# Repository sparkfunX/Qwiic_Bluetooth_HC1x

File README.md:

SparkFun Qwiic Bluetooth
========================================

[*SparkX Qwiic Bluetooth (SPX-14840)*](https://www.sparkfun.com/products/14840)

Bluetooth is a great addition to a variety of projects, but the interface to most Bluetooth modules is through a serial UART, which can be a real bummer -- serial port availability can be limited and they're not always super-reliable. The Qwiic Bluetooth aims resolve that issue by providing an I<sup>2</sup>C interface to the HM-13 Bluetooth module.

This board's HM-13 Bluetooth module supports both SPP (Serial Port Profile) and BLE (Bluetooth low-energy) Bluetooth profiles via Bluetooth 4.0. The HM-13's support for BLE means it's compatible with any smartphone.  Or you can connect it to a computer via the old standard -- SPP -- and use it as a transparent Bluetooth data gateway. You can even use it in dual-mode, connected to a pair of devices simultaneously!

The board also features an ATTiny85, which has custom firmware to translate between between I<sup>2</sup>C and serial. There are a pair of Qwiic connectors, which allow you to string a variety of sensors up to a single I<sup>2</sup>C bus. Finally, a green "CON" LED indicates connection status -- blinking when disconnected and solid when connected.

Check out our [HM-13 Arduino library](https://github.com/sparkfun/SparkFun_HM1X_Bluetooth_Arduino_Library) for help developing Bluetooth app of your own! There are a handful of "Qwiic" examples, which demonstrate how to set up a simple serial passthrough, adjust some of the module settings, and even set it up as an **iBeacon**.

SparkFun labored with love to create this code. Feel like supporting open source hardware? 
Buy a [breakout board](https://www.sparkfun.com/products/14840) from SparkFun!

Repository Contents
-------------------

* **/Documents** - Datasheets
* **/Firmware** - I<sup>2</sup>C-to-Serial firmware for ATTiny85 (Arduino code)
* **/Hardware** - Eagle design files (.brd, .sch)

License Information
-------------------

This product is _**open source**_! 

If you have any questions or concerns on licensing, please contact techsupport@sparkfun.com.

Please use, reuse, and modify these files as you see fit. Please maintain attribution to SparkFun Electronics and release any derivative under the same license.

Distributed as-is; no warranty is given.

- Your friends at SparkFun.

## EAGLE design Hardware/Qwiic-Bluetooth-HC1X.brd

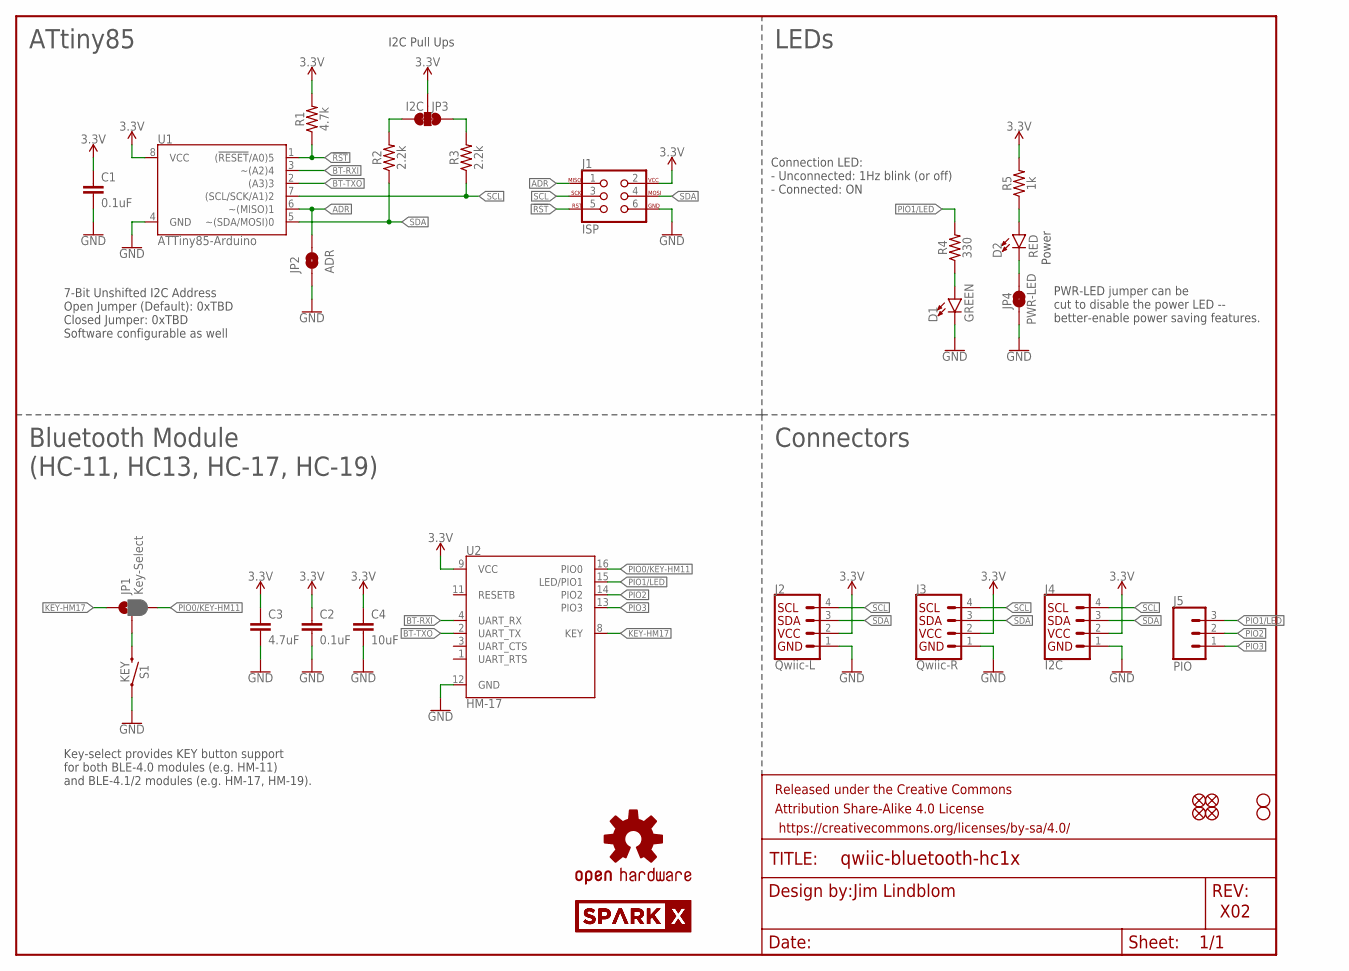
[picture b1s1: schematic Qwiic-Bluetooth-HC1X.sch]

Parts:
C1, C2: 0.1uF; 0603
C3: 4.7uF; 0603
C4: 10uF; 0603
D1: GREEN; LED-0603
D2: RED; LED-0603
FRAME1: FRAME-LETTER; CREATIVE_COMMONS
J1: ISP; 2X3_TEST_POINTS
J2: Qwiic-L; 1X04_1MM_RA
J3: Qwiic-R; 1X04_1MM_RA
J4: I2C; 1X04_NO_SILK
J5: PIO; 1X03_NO_SILK
JP1: Key-Select; SMT-JUMPER_3_1-NC_PASTE_NO-SILK
JP2: ADR; SMT-JUMPER_2_NO_NO-SILK
JP3: I2C; SMT-JUMPER_3_2-NC_TRACE_NO-SILK
JP4: PWR-LED; SMT-JUMPER_2_NC_TRACE_NO-SILK
JP5, JP6, JP7, JP8: FIDUCIALUFIDUCIAL; FIDUCIAL-MICRO
JP11, JP12: STAND-OFF
LOGO1: OSHW-LOGOMINI; OSHW-LOGO-MINI
LOGO2, LOGO3: SPARKX-LOGO4; SPARKX-MEDIUM
R1: 4.7k; 0603
R2, R3: 2.2k; 0603
R4: 330; 0603
R5: 1k; 0603
S1: KEY; TACTILE_SWITCH_SMD_4.6X2.8MM
U1: ATTiny85-Arduino; SO08-EIAJ_MCU
U2: HM-17; HM-11

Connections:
3.3V: C1.1, C2.1, C3.1, C4.1, J1.2, J2.2, J3.2, J4.2 (VCC), JP3.2, R1.2, R5.2, U1.8 (VCC), U2.9 (VCC)
!RST: J1.5, R1.1, U1.1 ((!RESET!/A0)5)
ADR: J1.1, JP2.2, U1.6 (~(MISO)1)
BT-RXI: U1.3 (~(A2)4), U2.4 (UART_RX)
BT-TXO: U1.2 ((A3)3), U2.2 (UART_TX)
GND: C1.2, C2.2, C3.2, C4.2, D1.C, J1.6, J2.1, J3.1, J4.1 (GND), JP2.1, JP4.1, S1.1, S1.2 (1), U1.4 (GND), U2.12 (GND)
KEY-HM17: JP1.1, U2.8 (KEY)
unnamed: D2.C, JP4.2
unnamed: D1.A, R4.1
unnamed: D2.A, R5.1
unnamed: JP1.2, S1.3 (2), S1.4 (2)
PIO0/KEY-HM11: JP1.3, U2.16 (PIO0)
PIO1/LED: J5.3, R4.2, U2.15 (LED/PIO1)
PIO2: J5.2, U2.14 (PIO2)
PIO3: J5.1, U2.13 (PIO3)
SCL: J1.3, J2.4, J3.4, J4.4 (SCL), R3.1, U1.7 ((SCL/SCK/A1)2)
SCL_PU1: JP3.1, R3.2
SDA: J1.4, J2.3, J3.3, J4.3 (SDA), R2.1, U1.5 (~(SDA/MOSI)0)
SDA_PU1: JP3.3, R2.2

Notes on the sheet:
7-Bit Unshifted I2C Address Open Jumper (Default): 0xTBD Closed Jumper: 0xTBD Software configurable as well
I2C Pull Ups
ATtiny85
Jim Lindblom
X02
Power
Key-select provides KEY button support for both BLE-4.0 modules (e.g. HM-11) and BLE-4.1/2 modules (e.g. HM-17, HM-19).
PWR-LED jumper can be cut to disable the power LED -- better-enable power saving features.
Bluetooth Module (HC-11, HC13, HC-17, HC-19)
LEDs
Connectors
Connection LED: - Unconnected: 1Hz blink (or off) - Connected: ON

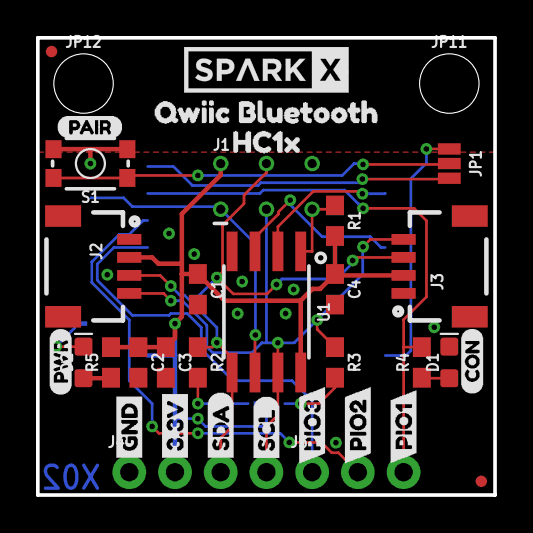
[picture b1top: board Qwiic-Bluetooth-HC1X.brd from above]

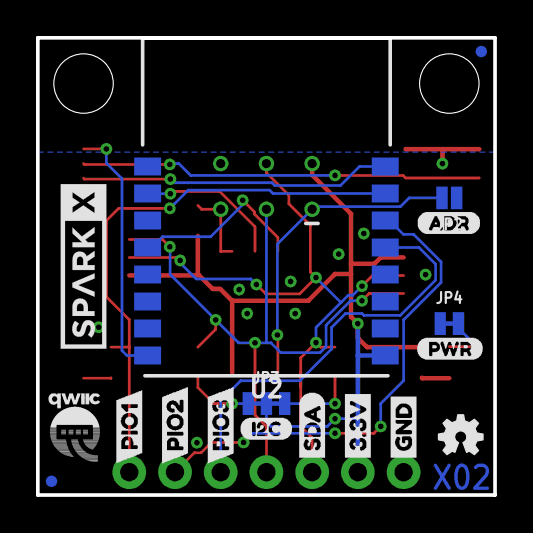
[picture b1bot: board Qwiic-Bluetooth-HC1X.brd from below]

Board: 2 copper layers, 25.4 x 25.4 mm, 55 parts (18 on the bottom side), 19 nets.

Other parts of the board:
U$1, U$6: SDA4
U$2: HC1X12
U$3, U$22: PIO110
U$4, U$10: GND0
U$5, U$11: 3#3V1
U$7: SCL2
U$8, U$14: PIO33
U$9, U$15: PIO29
U$13, U$16: PWR5
U$17: CON13
U$18: QWIIC_BLUETOOTH11
U$19: ADR8
U$20: I2C7
U$21: QWIIC-LOGO-SMALL
U$23: PAIR15

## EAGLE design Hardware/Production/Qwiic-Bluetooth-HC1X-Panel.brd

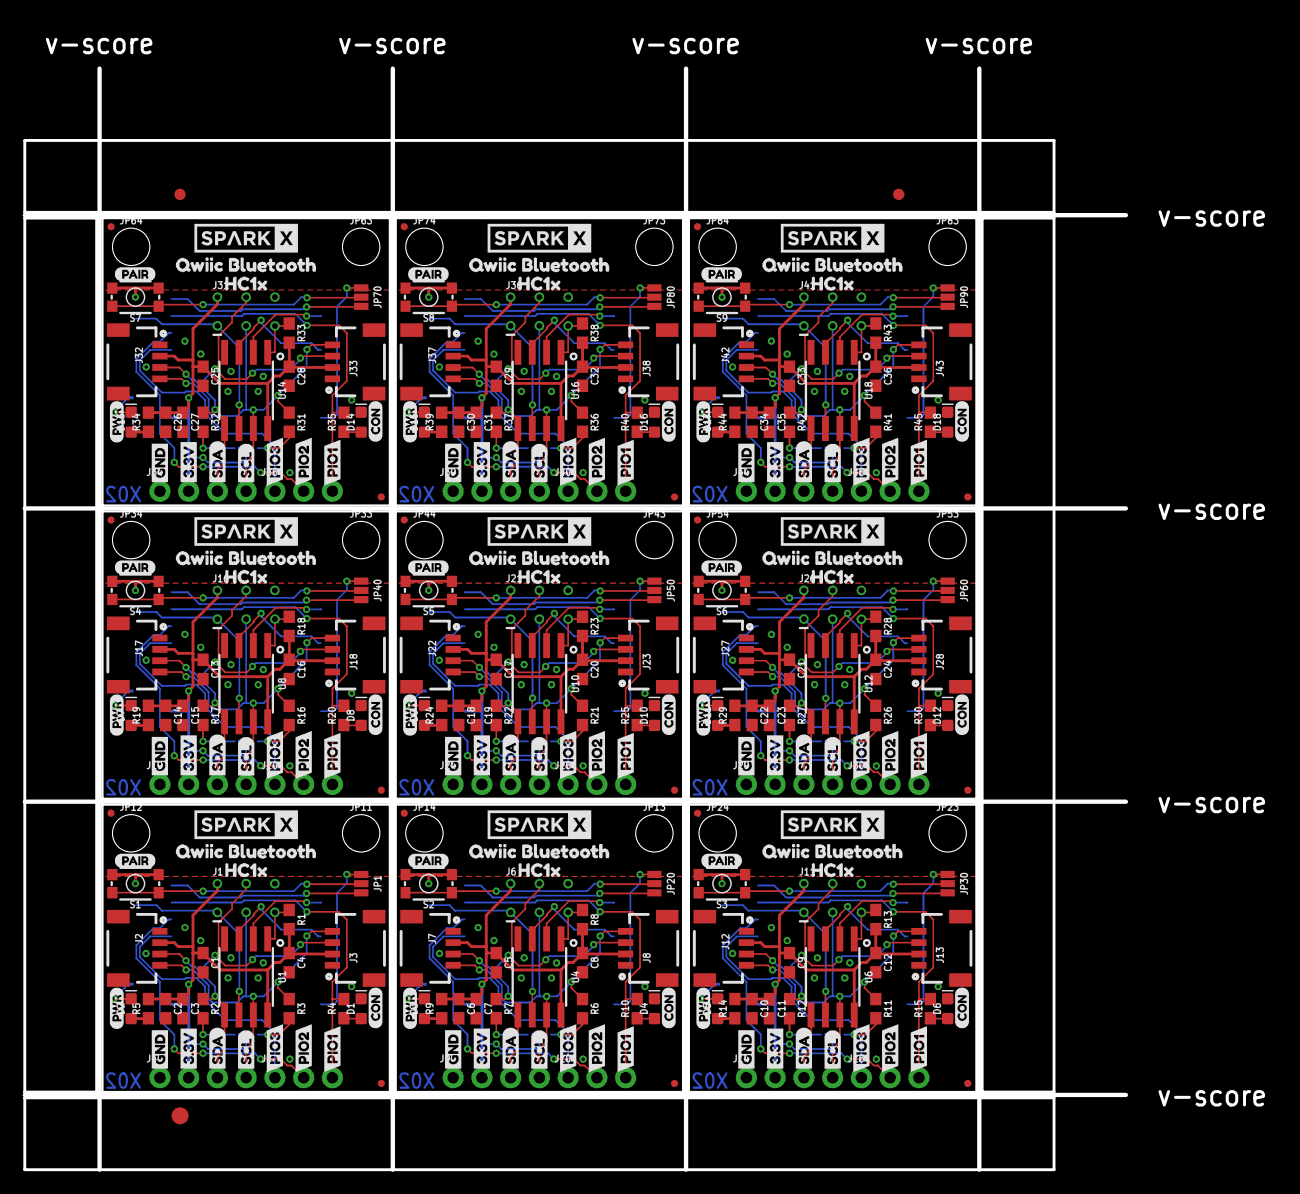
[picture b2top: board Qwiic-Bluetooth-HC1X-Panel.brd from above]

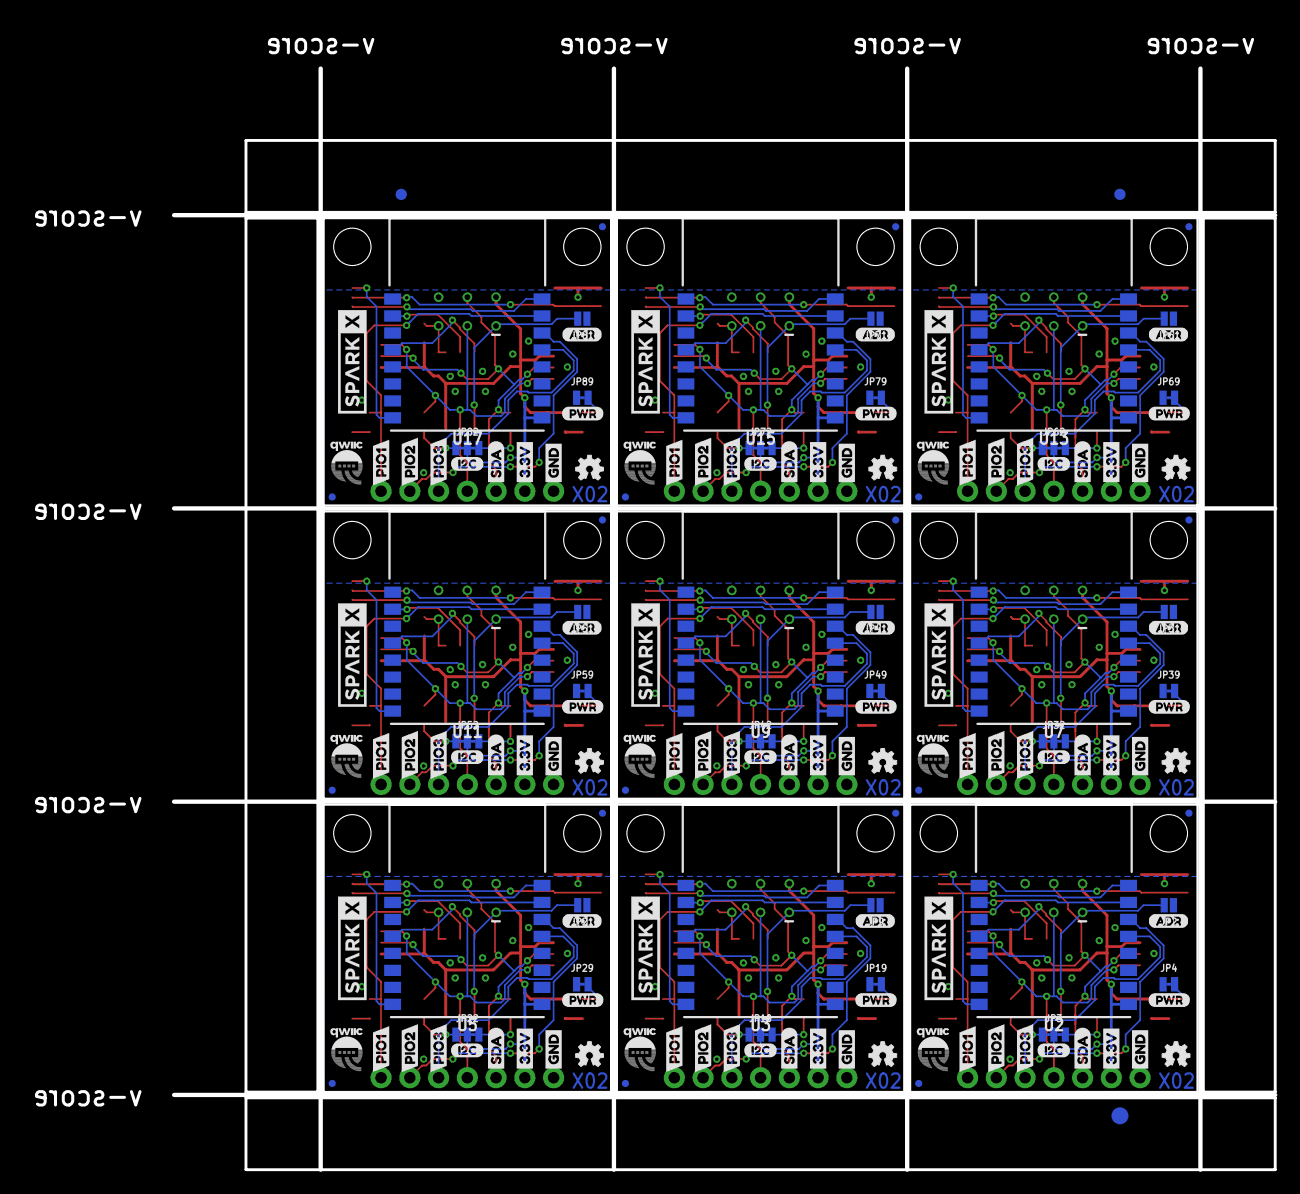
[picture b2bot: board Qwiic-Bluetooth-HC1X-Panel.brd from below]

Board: 2 copper layers, 110.5 x 101.2 mm, 492 parts (165 on the bottom side), 171 nets.

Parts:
C1, C2, C5, C6, C9, C10, C13, C14, C17, C18, C21, C22, C25, C26, C29, C30, C33, C34: 0.1uF; 0603
C3, C7, C11, C15, C19, C23, C27, C31, C35: 4.7uF; 0603
C4, C8, C12, C16, C20, C24, C28, C32, C36: 10uF; 0603
D1, D4, D6, D8, D10, D12, D14, D16, D18: GREEN; LED-0603
D2, D3, D5, D7, D9, D11, D13, D15, D17: RED; LED-0603
E$1, E$2, E$3, E$4: FIDUCIAL-1X2
E$5, E$6: FIDUCIAL-1.5X3
J1, J6, J11, J16, J21, J26, J31, J36, J41: ISP; 2X3_TEST_POINTS
J2, J7, J12, J17, J22, J27, J32, J37, J42: Qwiic-L; 1X04_1MM_RA
J3, J8, J13, J18, J23, J28, J33, J38, J43: Qwiic-R; 1X04_1MM_RA
J4, J9, J14, J19, J24, J29, J34, J39, J44: I2C; 1X04_NO_SILK
J5, J10, J15, J20, J25, J30, J35, J40, J45: PIO; 1X03_NO_SILK
JP1, JP20, JP30, JP40, JP50, JP60, JP70, JP80, JP90: Key-Select; SMT-JUMPER_3_1-NC_PASTE_NO-SILK
JP2, JP9, JP21, JP31, JP41, JP51, JP61, JP71, JP81: ADR; SMT-JUMPER_2_NO_NO-SILK
JP3, JP10, JP22, JP32, JP42, JP52, JP62, JP72, JP82: I2C; SMT-JUMPER_3_2-NC_TRACE_NO-SILK
JP4, JP19, JP29, JP39, JP49, JP59, JP69, JP79, JP89: PWR-LED; SMT-JUMPER_2_NC_TRACE_NO-SILK
JP5, JP6, JP7, JP8, JP15, JP16, JP17, JP18, JP25, JP26, JP27, JP28, JP35, JP36, JP37, JP38, JP45, JP46, JP47, JP48, JP55, JP56, JP57, JP58, JP65, JP66, JP67, JP68, JP75, JP76, JP77, JP78, JP85, JP86, JP87, JP88: FIDUCIALUFIDUCIAL; FIDUCIAL-MICRO
JP11, JP12, JP13, JP14, JP23, JP24, JP33, JP34, JP43, JP44, JP53, JP54, JP63, JP64, JP73, JP74, JP83, JP84: STAND-OFF
LOGO1, LOGO5, LOGO8, LOGO11, LOGO14, LOGO17, LOGO20, LOGO23, LOGO26: OSHW-LOGOMINI; OSHW-LOGO-MINI
LOGO2, LOGO3, LOGO4, LOGO6, LOGO7, LOGO9, LOGO10, LOGO12, LOGO13, LOGO15, LOGO16, LOGO18, LOGO19, LOGO21, LOGO22, LOGO24, LOGO25, LOGO27: SPARKX-LOGO4; SPARKX-MEDIUM
R1, R8, R13, R18, R23, R28, R33, R38, R43: 4.7k; 0603
R2, R3, R6, R7, R11, R12, R16, R17, R21, R22, R26, R27, R31, R32, R36, R37, R41, R42: 2.2k; 0603
R4, R10, R15, R20, R25, R30, R35, R40, R45: 330; 0603
R5, R9, R14, R19, R24, R29, R34, R39, R44: 1k; 0603
S1, S2, S3, S4, S5, S6, S7, S8, S9: KEY; TACTILE_SWITCH_SMD_4.6X2.8MM
U1, U4, U6, U8, U10, U12, U14, U16, U18: ATTiny85-Arduino; SO08-EIAJ_MCU
U2, U3, U5, U7, U9, U11, U13, U15, U17: HM-17; HM-11
U$1, U$6, U$25, U$40, U$47, U$62, U$69, U$84, U$91, U$106, U$113, U$128, U$135, U$150, U$157, U$172, U$179, U$194: SDA4
U$2, U$43, U$65, U$87, U$109, U$131, U$153, U$175, U$197: HC1X12
U$3, U$22, U$41, U$42, U$63, U$64, U$85, U$86, U$107, U$108, U$129, U$130, U$151, U$152, U$173, U$174, U$195, U$196: PIO110
U$4, U$10, U$12, U$29, U$45, U$51, U$67, U$73, U$89, U$95, U$111, U$117, U$133, U$139, U$155, U$161, U$177, U$183: GND0
U$5, U$11, U$24, U$30, U$46, U$52, U$68, U$74, U$90, U$96, U$112, U$118, U$134, U$140, U$156, U$162, U$178, U$184: 3#3V1
U$7, U$26, U$48, U$70, U$92, U$114, U$136, U$158, U$180: SCL2
U$8, U$14, U$27, U$31, U$49, U$53, U$71, U$75, U$93, U$97, U$115, U$119, U$137, U$141, U$159, U$163, U$181, U$185: PIO33
U$9, U$15, U$28, U$32, U$50, U$54, U$72, U$76, U$94, U$98, U$116, U$120, U$138, U$142, U$160, U$164, U$182, U$186: PIO29
U$13, U$16, U$33, U$38, U$55, U$60, U$77, U$82, U$99, U$104, U$121, U$126, U$143, U$148, U$165, U$170, U$187, U$192: PWR5
U$17, U$34, U$56, U$78, U$100, U$122, U$144, U$166, U$188: CON13
U$18, U$35, U$57, U$79, U$101, U$123, U$145, U$167, U$189: QWIIC_BLUETOOTH11
U$19, U$36, U$58, U$80, U$102, U$124, U$146, U$168, U$190: ADR8
U$20, U$37, U$59, U$81, U$103, U$125, U$147, U$169, U$191: I2C7
U$21, U$39, U$61, U$83, U$105, U$127, U$149, U$171, U$193: QWIIC-LOGO-SMALL
U$23, U$44, U$66, U$88, U$110, U$132, U$154, U$176, U$198: PAIR15

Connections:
3.3V: C1.1, C2.1, C3.1, C4.1, J1.2, J2.2, J3.2, J4.2, JP3.2, R1.2, R5.2, U1.8, U2.9
3.3V1: C5.1, C6.1, C7.1, C8.1, J6.2, J7.2, J8.2, J9.2, JP10.2, R8.2, R9.2, U3.9, U4.8
3.3V2: C9.1, C10.1, C11.1, C12.1, J11.2, J12.2, J13.2, J14.2, JP22.2, R13.2, R14.2, U5.9, U6.8
3.3V3: C13.1, C14.1, C15.1, C16.1, J16.2, J17.2, J18.2, J19.2, JP32.2, R18.2, R19.2, U7.9, U8.8
3.3V4: C17.1, C18.1, C19.1, C20.1, J21.2, J22.2, J23.2, J24.2, JP42.2, R23.2, R24.2, U9.9, U10.8
3.3V5: C21.1, C22.1, C23.1, C24.1, J26.2, J27.2, J28.2, J29.2, JP52.2, R28.2, R29.2, U11.9, U12.8
3.3V6: C25.1, C26.1, C27.1, C28.1, J31.2, J32.2, J33.2, J34.2, JP62.2, R33.2, R34.2, U13.9, U14.8
3.3V7: C29.1, C30.1, C31.1, C32.1, J36.2, J37.2, J38.2, J39.2, JP72.2, R38.2, R39.2, U15.9, U16.8
3.3V8: C33.1, C34.1, C35.1, C36.1, J41.2, J42.2, J43.2, J44.2, JP82.2, R43.2, R44.2, U17.9, U18.8
!RST: J1.5, R1.1, U1.1
!RST1: J6.5, R8.1, U4.1
!RST2: J11.5, R13.1, U6.1
!RST3: J16.5, R18.1, U8.1
!RST4: J21.5, R23.1, U10.1
!RST5: J26.5, R28.1, U12.1
!RST6: J31.5, R33.1, U14.1
!RST7: J36.5, R38.1, U16.1
!RST8: J41.5, R43.1, U18.1
ADR: J1.1, JP2.2, U1.6
ADR1: J6.1, JP9.2, U4.6
ADR2: J11.1, JP21.2, U6.6
ADR3: J16.1, JP31.2, U8.6
ADR4: J21.1, JP41.2, U10.6
ADR5: J26.1, JP51.2, U12.6
ADR6: J31.1, JP61.2, U14.6
ADR7: J36.1, JP71.2, U16.6
ADR8: J41.1, JP81.2, U18.6
BT-RXI: U1.3, U2.4
BT-RXI1: U3.4, U4.3
BT-RXI2: U5.4, U6.3
BT-RXI3: U7.4, U8.3
BT-RXI4: U9.4, U10.3
BT-RXI5: U11.4, U12.3
BT-RXI6: U13.4, U14.3
BT-RXI7: U15.4, U16.3
BT-RXI8: U17.4, U18.3
BT-TXO: U1.2, U2.2
BT-TXO1: U3.2, U4.2
BT-TXO2: U5.2, U6.2
BT-TXO3: U7.2, U8.2
BT-TXO4: U9.2, U10.2
BT-TXO5: U11.2, U12.2
BT-TXO6: U13.2, U14.2
BT-TXO7: U15.2, U16.2
BT-TXO8: U17.2, U18.2
GND: C1.2, C2.2, C3.2, C4.2, D1.C, J1.6, J2.1, J3.1, J4.1, JP2.1, JP4.1, S1.1, S1.2, U1.4, U2.12
GND1: C5.2, C6.2, C7.2, C8.2, D4.C, J6.6, J7.1, J8.1, J9.1, JP9.1, JP19.1, S2.1, S2.2, U3.12, U4.4
GND2: C9.2, C10.2, C11.2, C12.2, D6.C, J11.6, J12.1, J13.1, J14.1, JP21.1, JP29.1, S3.1, S3.2, U5.12, U6.4
GND3: C13.2, C14.2, C15.2, C16.2, D8.C, J16.6, J17.1, J18.1, J19.1, JP31.1, JP39.1, S4.1, S4.2, U7.12, U8.4
GND4: C17.2, C18.2, C19.2, C20.2, D10.C, J21.6, J22.1, J23.1, J24.1, JP41.1, JP49.1, S5.1, S5.2, U9.12, U10.4
GND5: C21.2, C22.2, C23.2, C24.2, D12.C, J26.6, J27.1, J28.1, J29.1, JP51.1, JP59.1, S6.1, S6.2, U11.12, U12.4
GND6: C25.2, C26.2, C27.2, C28.2, D14.C, J31.6, J32.1, J33.1, J34.1, JP61.1, JP69.1, S7.1, S7.2, U13.12, U14.4
GND7: C29.2, C30.2, C31.2, C32.2, D16.C, J36.6, J37.1, J38.1, J39.1, JP71.1, JP79.1, S8.1, S8.2, U15.12, U16.4
GND8: C33.2, C34.2, C35.2, C36.2, D18.C, J41.6, J42.1, J43.1, J44.1, JP81.1, JP89.1, S9.1, S9.2, U17.12, U18.4
KEY-HM1: JP20.1, U3.8
KEY-HM2: JP30.1, U5.8
KEY-HM3: JP40.1, U7.8
KEY-HM4: JP50.1, U9.8
KEY-HM5: JP60.1, U11.8
KEY-HM6: JP70.1, U13.8
KEY-HM7: JP80.1, U15.8
KEY-HM8: JP90.1, U17.8
KEY-HM17: JP1.1, U2.8
unnamed: D2.C, JP4.2
unnamed: D1.A, R4.1
unnamed: D2.A, R5.1
unnamed: JP1.2, S1.3, S1.4
unnamed: D3.A, R9.1
unnamed: D3.C, JP19.2
unnamed: D4.A, R10.1
unnamed: JP20.2, S2.3, S2.4
unnamed: D5.A, R14.1
unnamed: D5.C, JP29.2
unnamed: D6.A, R15.1
unnamed: JP30.2, S3.3, S3.4
unnamed: D7.A, R19.1
unnamed: D7.C, JP39.2
unnamed: D8.A, R20.1
unnamed: JP40.2, S4.3, S4.4
unnamed: D9.A, R24.1
unnamed: D9.C, JP49.2
unnamed: D10.A, R25.1
unnamed: JP50.2, S5.3, S5.4
unnamed: D11.A, R29.1
unnamed: D11.C, JP59.2
unnamed: D12.A, R30.1
unnamed: JP60.2, S6.3, S6.4
unnamed: D13.A, R34.1
unnamed: D13.C, JP69.2
unnamed: D14.A, R35.1
unnamed: JP70.2, S7.3, S7.4
unnamed: D15.A, R39.1
unnamed: D15.C, JP79.2
unnamed: D16.A, R40.1
unnamed: JP80.2, S8.3, S8.4
unnamed: D17.A, R44.1
unnamed: D17.C, JP89.2
unnamed: D18.A, R45.1
unnamed: JP90.2, S9.3, S9.4
PIO0/KEY-HM1: JP20.3, U3.16
PIO0/KEY-HM2: JP30.3, U5.16
PIO0/KEY-HM3: JP40.3, U7.16
PIO0/KEY-HM4: JP50.3, U9.16
PIO0/KEY-HM5: JP60.3, U11.16
PIO0/KEY-HM6: JP70.3, U13.16
PIO0/KEY-HM7: JP80.3, U15.16
PIO0/KEY-HM8: JP90.3, U17.16
PIO0/KEY-HM11: JP1.3, U2.16
PIO1: J10.2, U3.14
PIO1/LED: J5.3, R4.2, U2.15
PIO1/LED1: J10.3, R10.2, U3.15
PIO1/LED2: J15.3, R15.2, U5.15
PIO1/LED3: J20.3, R20.2, U7.15
PIO1/LED4: J25.3, R25.2, U9.15
PIO1/LED5: J30.3, R30.2, U11.15
PIO1/LED6: J35.3, R35.2, U13.15
PIO1/LED7: J40.3, R40.2, U15.15
PIO1/LED8: J45.3, R45.2, U17.15
PIO2: J5.2, U2.14
PIO3: J5.1, U2.13
PIO4: J10.1, U3.13
PIO5: J15.2, U5.14
PIO6: J15.1, U5.13
PIO7: J20.2, U7.14
PIO8: J20.1, U7.13
PIO9: J25.2, U9.14
PIO10: J25.1, U9.13
PIO11: J30.2, U11.14
PIO12: J30.1, U11.13
PIO13: J35.2, U13.14
PIO14: J35.1, U13.13
PIO15: J40.2, U15.14
PIO16: J40.1, U15.13
PIO17: J45.2, U17.14
PIO18: J45.1, U17.13
SCL: J1.3, J2.4, J3.4, J4.4, R3.1, U1.7
SCL1: J6.3, J7.4, J8.4, J9.4, R6.1, U4.7
SCL2: J11.3, J12.4, J13.4, J14.4, R11.1, U6.7
SCL3: J16.3, J17.4, J18.4, J19.4, R16.1, U8.7
SCL4: J21.3, J22.4, J23.4, J24.4, R21.1, U10.7
SCL5: J26.3, J27.4, J28.4, J29.4, R26.1, U12.7
SCL6: J31.3, J32.4, J33.4, J34.4, R31.1, U14.7
SCL7: J36.3, J37.4, J38.4, J39.4, R36.1, U16.7
SCL8: J41.3, J42.4, J43.4, J44.4, R41.1, U18.7
SCL_PU1: JP3.1, R3.2
SCL_PU2: JP10.1, R6.2
SCL_PU3: JP22.1, R11.2
SCL_PU4: JP32.1, R16.2
SCL_PU5: JP42.1, R21.2
SCL_PU6: JP52.1, R26.2
SCL_PU7: JP62.1, R31.2
SCL_PU8: JP72.1, R36.2
SCL_PU9: JP82.1, R41.2
SDA: J1.4, J2.3, J3.3, J4.3, R2.1, U1.5
SDA1: J6.4, J7.3, J8.3, J9.3, R7.1, U4.5
SDA2: J11.4, J12.3, J13.3, J14.3, R12.1, U6.5
SDA3: J16.4, J17.3, J18.3, J19.3, R17.1, U8.5
SDA4: J21.4, J22.3, J23.3, J24.3, R22.1, U10.5
SDA5: J26.4, J27.3, J28.3, J29.3, R27.1, U12.5
SDA6: J31.4, J32.3, J33.3, J34.3, R32.1, U14.5
SDA7: J36.4, J37.3, J38.3, J39.3, R37.1, U16.5
SDA8: J41.4, J42.3, J43.3, J44.3, R42.1, U18.5
SDA_PU1: JP3.3, R2.2
SDA_PU2: JP10.3, R7.2
SDA_PU3: JP22.3, R12.2
SDA_PU4: JP32.3, R17.2
SDA_PU5: JP42.3, R22.2
SDA_PU6: JP52.3, R27.2
SDA_PU7: JP62.3, R32.2
SDA_PU8: JP72.3, R37.2
SDA_PU9: JP82.3, R42.2

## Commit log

2018-05-15 initial commit of hardware
2018-05-15 Adding HC1x documentation.
2018-05-15 Adding decoupling, fixing silk.
2018-05-15 Adding 3x3 panel and gerber.
2018-05-24 Fixing HM-17 pinout, and revising layout to x02
2018-05-24 Pushing production panel for x02.
2018-07-02 Initial commit of ATtiny firmware
2018-07-10 Adding firmware hex file and an example batch programming script.
2018-07-10 Adding content to README

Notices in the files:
parts and their libraries:
SparkFun-Capacitors: Licensing: Creative Commons ShareAlike 4.0 International - https://creativecommons.org/licenses/by-sa/4.0
SparkFun-Aesthetics: Released under the Creative Commons Attribution Share-Alike 4.0 License
SparkFun-Aesthetics: https://creativecommons.org/licenses/by-sa/4.0
